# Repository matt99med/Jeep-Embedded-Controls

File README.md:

# Jeep Embedded Controls

A custom embedded security and control system for a 1995 Jeep Wrangler, built as a
personal project to demonstrate full-stack embedded systems development across firmware,
hardware, PCB design, power electronics, and mobile applications.

## Project Overview

This system provides remote control, alarm/immobilization, and real-time GPS tracking
for a 1995 Jeep Wrangler using two custom-designed PCBs, 3D printed enclosures, and a
companion web app. A keyfob and a main controller communicate wirelessly via ESP-NOW,
with 4G LTE cellular for remote GPS tracking accessible from any device.

The system is designed around a **battery-backed, low-power security architecture**: the
controller runs from its own auxiliary battery so it keeps tracking and alarming even if
the vehicle's main battery is disconnected — the exact scenario a theft involves — while
never drawing the vehicle battery down when parked.

## Demo

> Live GPS tracker web app: [Jeep Tracker](https://matt99med.github.io/Jeep-Embedded-Controls/)

## Features

- Remote kill switch (immobilizer) via custom ESP-NOW keyfob
- **Hidden manual bypass switch** — fail-safe so a controller fault never strands the vehicle
- Hood and shock sensor triggered siren with automatic arming
- Remote arm/disarm via keyfob with LED status feedback
- Real-time GPS tracking via 4G LTE cellular (SIM7600G-H)
- Web app for live location tracking via MQTT over HiveMQ Cloud
- **Auxiliary backup battery** — system survives main-battery disconnect
- **Vehicle-sensing charge control** — aux battery charges only while the alternator runs,
  so the vehicle battery is never drained while parked (months of standby)
- **Deep-sleep architecture** — wakes on hood/shock/timer events; tens of µA when parked
- Hardware low-voltage disconnect protecting the aux battery from over-discharge
- LiPo battery powered keyfob with USB-C charging

## Hardware

### Main Controller

- **ESP32-WROOM-32E** module (240MHz dual-core, Wi-Fi, BT)
- **CP2102N** USB-to-UART bridge with auto-reset programming circuit (USB-C)
- **SIM7600G-H** 4G LTE + GPS (Waveshare breakout, socketed)
- **Auxiliary battery system:** 12V sealed AGM battery
- **Vehicle-sensing charge relay:** connects vehicle 12V to aux battery only when the
  alternator is running (firmware-controlled, AO3400A driver, off-board relay)
- **Power rails:**
  - LM5164-Q1 wide-Vin synchronous buck (battery -> 3.3V, ~10uA quiescent)
  - MP2307DN buck (battery -> 3.8V for SIM7600, gated by GPIO for sleep)
  - Hardware UVLO low-voltage disconnect on the 3.3V buck
- Relay/fuse box for kill switch + siren (off-board high current)
- BAT54S input clamps + RC filtering on hood/shock sensor inputs
- SMCJ33A TVS protection on 12V inputs
- 4 firmware-controlled status LEDs (system / cellular / armed / fault)
- Custom 2-layer KiCad PCB, 154.5 x 120 mm
- Custom Fusion 360 enclosure (in progress)

### Keyfob

- **ESP32-C3FH4X** (bare QFN32, 160MHz RISC-V, in-package 4MB flash)
- **Johanson 2450AT18A100E-AEC** chip antenna with L-C-L matching network
- 40MHz crystal (NX3225GD-40M)
- MCP73831 LiPo charger IC
- 3.7V LiPo battery
- USB-C charging + native USB programming (GPIO18/19)
- AP2112K-3.3 LDO
- Tactile buttons: Lock, Unlock + BOOT/RESET
- Status LEDs: charge + connection
- Slide power switch
- Custom 2-layer KiCad PCB, 30 x 50 mm
- Custom Fusion 360 enclosure (in progress)

## Tech Stack

| Category        | Technology                            |
| --------------- | ------------------------------------- |
| Firmware        | ESP-IDF v6.0 (C)                      |
| RTOS            | FreeRTOS                              |
| Wireless        | ESP-NOW (keyfob <-> controller)       |
| Cellular        | SIM7600G-H AT commands over UART2     |
| IoT Protocol    | MQTT over TLS (HiveMQ Cloud)          |
| PCB Design      | KiCad 10.0                            |
| 3D Modeling     | Autodesk Fusion 360                   |
| Web App         | HTML/CSS/JavaScript + Google Maps API |
| Version Control | Git/GitHub                            |
| PCB Fabrication | JLCPCB (assembled)                    |

## System Architecture

```
[Keyfob ESP32-C3] <--ESP-NOW 2.4GHz--> [Main ESP32 Controller]
[Lock/Unlock]                            [Kill Switch / Siren]
                                         [Hood + Shock Sensors]
                                         [Aux Battery + Charge Control]
                                         [Hidden Bypass Switch]
                                                 |
                                         [SIM7600G-H Module]
                                                 |
                                      [Hologram IoT SIM / 4G LTE]
                                                 |
                                        [HiveMQ MQTT Broker]
                                                 |
                                     [Web App / iPhone / Any Device]
```

## Power Architecture

```
[Vehicle 12V] --fused--> [Charge Relay] --(only when alternator running)--> [Aux 12V Battery]
                              ^                                                    |
                       [GPIO sense/control]                                        |
                                                                                   v
                                                          +------------------------+
                                                          |                        |
                                                  [LM5164 Buck]            [MP2307 Buck]
                                                   3.3V (always-on,         3.8V (gated,
                                                   UVLO protected)          SIM7600)
                                                          |                        |
                                                  [ESP32 + logic]          [SIM7600G-H]
```

Key property: when parked, the vehicle battery and the aux battery are physically
disconnected. The controller draws only from the aux battery, so the vehicle always
starts no matter how long it sits.

## Firmware Architecture

The main controller firmware is built around a **tiered low-power state machine** rather
than always-on tasks, to achieve months of parked standby on the auxiliary battery.

### Operating Model

- **Deep sleep** is the default parked state — modem off, CPU halted, only RTC wake
  sources armed. Draw is in the tens of uA.
- **Wake sources:** hood sensor (RTC GPIO), shock sensor (RTC GPIO), or a wake timer for
  scheduled MQTT check-ins. The check-in interval shortens automatically when armed.
- **Active window:** after any activity the controller stays in *light sleep* so the
  radio remains listenable, giving near-instant ESP-NOW lock/unlock response. After an
  idle timeout it drops back to deep sleep.
- On every wake the controller reads vehicle + battery voltage, runs charge control, and
  — if armed and triggered — fires the siren, immobilizes, and pushes an alert + GPS
  burst over cellular.

### Kill Relay Logic (fail-safe)

The kill relay is **energized-to-run**: driving the coil HIGH closes the starter circuit
(vehicle can start); LOW immobilizes. A dead controller, dead battery, or cut wire
therefore fails *immobilized*, and the hidden mechanical bypass switch is the recovery
path. The bypass is intentionally not wired to the PCB.

### Charge Control

Firmware closes the charge relay above 13.2 V on the vehicle-sense line (alternator
running) and opens it below 12.8 V, with hysteresis to avoid chatter. The relay coil is
fed from the vehicle side, so charging is physically impossible when the engine is off
regardless of firmware state.

### Source Layout

```
main_controller/main/
├── main.c            # wake-reason dispatch, tiered sleep state machine
├── config.h          # pin map, thresholds, ESP-NOW protocol
├── system_state.h    # shared state + arm/alarm/charge API
├── gpio_handler.c    # ADC sensing, relay control, arm/alarm, charge logic
├── espnow_handler.c  # keyfob command receiver
└── sim7600.c         # modem power sequencing, GPS, MQTT

keyfob/main/
├── main.c            # deep-sleep wake-on-button, send, LED ack, sleep
├── config.h          # pin map + ESP-NOW protocol
├── espnow_keyfob.c   # one-shot ESP-NOW transmit
└── espnow_keyfob.h
```

### ESP-NOW Message Protocol

| Command     | Value | Action                             |
| ----------- | ----- | ---------------------------------- |
| CMD_LOCK    | 0x01  | Arm siren + immobilize (kill LOW)  |
| CMD_UNLOCK  | 0x02  | Disarm + allow run (kill HIGH)     |

### MQTT Topics

| Topic            | Direction   | Payload                     |
| ---------------- | ----------- | --------------------------- |
| jeep/gps/request | App -> ESP32 | "request"                  |
| jeep/gps/data    | ESP32 -> App | {"lat":xx.xxx,"lon":xx.xxx} |
| jeep/status      | ESP32 -> App | "armed" or "disarmed"       |
| jeep/alert       | ESP32 -> App | power-cut / tamper event    |

> Broker credentials and APN are provided via NVS / `idf.py menuconfig`, not committed to
> source.

## PCB Design

### Keyfob PCB

- 2-layer board, 30 x 50 mm
- All 0402 passives, JLCPCB assembled
- Bare ESP32-C3FH4X with Johanson chip antenna + matching network
- GND copper pour on B.Cu with via stitching
- M2 mounting holes
- USB-C edge connector for charging + programming
- **Status: ordered from JLCPCB (assembled) — awaiting delivery**

### Main Controller PCB

- 2-layer board, 154.5 x 120 mm
- Automotive environment rated design
- Bare ESP32-WROOM-32E + CP2102N programming
- Dual switching power supplies (LM5164 + MP2307)
- Aux battery charge management + UVLO
- Screw-terminal field wiring, socketed SIM7600 carrier
- GND copper pour on B.Cu with via stitching
- M3 mounting holes in all 4 corners
- **Status: ordered from JLCPCB (assembled) — awaiting delivery**

## Status

- [x] Hardware redesign complete (KiCad schematics — both boards, bare-chip)
- [x] Battery-backed power architecture with vehicle-sensing charge control
- [x] Firmware rework for deep-sleep / charge-control architecture
- [x] Keyfob PCB ordered (JLCPCB assembled)
- [x] Main controller PCB ordered (JLCPCB assembled)
- [ ] PCB bring-up and board-level testing
- [ ] SIM7600 MQTT/cellular integration (broker connect + report cycle)
- [ ] 3D printed enclosures (Fusion 360 — in progress)
- [ ] Hidden bypass switch installation
- [ ] System integration and testing
- [ ] Final installation in 1995 Jeep Wrangler

## Author

**Matthew Medina**

California State University Fullerton — BS/MS Computer Engineering

GitHub: [matt99med](https://github.com/matt99med)

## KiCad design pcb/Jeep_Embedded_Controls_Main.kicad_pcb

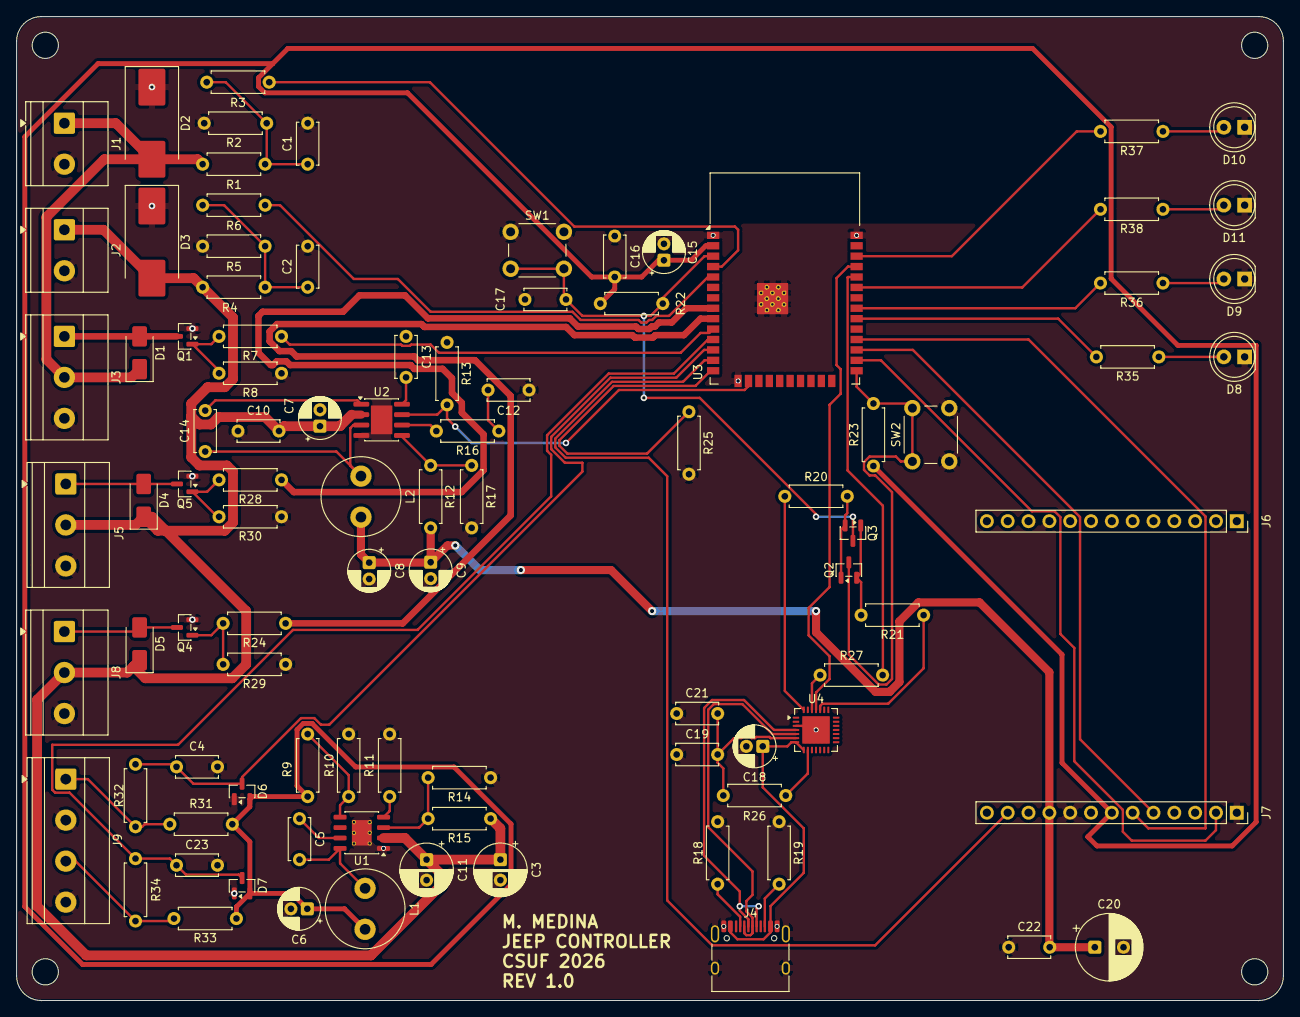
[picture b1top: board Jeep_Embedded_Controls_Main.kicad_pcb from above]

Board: 2 copper layers, 154.5 x 120.0 mm, 94 parts (0 on the bottom side), 63 nets.

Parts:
C1, C2, C4, C10, C13, C16, C19, C22, C23: 100nF; C_Disc_D5.0mm_W2.5mm_P5.00mm
C3: 2.2uF 100V; CP_Radial_D6.3mm_P2.50mm
C5: 100nF 16V; C_Disc_D5.0mm_W2.5mm_P5.00mm
C6: 47uF 10V; CP_Radial_D5.0mm_P2.00mm
C7: 10uF 25V; CP_Radial_D5.0mm_P2.00mm
C8, C9: 22uF 10V; CP_Radial_D5.0mm_P2.00mm
C11: 100uF; CP_Radial_D6.3mm_P2.50mm
C12: 3.9nF; C_Disc_D5.0mm_W2.5mm_P5.00mm
C14: 10nF; C_Disc_D5.0mm_W2.5mm_P5.00mm
C15, C18: 10uF; CP_Radial_D5.0mm_P2.00mm
C17, C21: 1uF; C_Disc_D5.0mm_W2.5mm_P5.00mm
C20: 220uF; CP_Radial_D8.0mm_P3.50mm
D1, D4, D5: SS14; D_SMA
D2, D3: SMCJ33A; D_SMC_Handsoldering
D6, D7: BAT54S; SOT-23
D8: D_SYS; LED_D5.0mm
D9: D_CELL; LED_D5.0mm
D10: D_ARM; LED_D5.0mm
D11: D_FAULT; LED_D5.0mm
J1: VBAT; TerminalBlock_Phoenix_MKDS-1,5-2_1x02_P5.00mm_Horizontal
J2: VAUX; TerminalBlock_Phoenix_MKDS-1,5-2_1x02_P5.00mm_Horizontal
J3: VCHARGE; TerminalBlock_Phoenix_MKDS-1,5-3_1x03_P5.00mm_Horizontal
J4: USB_C_Receptacle_USB2.0_16P; USB_C_Receptacle_HRO_TYPE-C-31-M-12
J5: KILL_SWITCH; TerminalBlock_Phoenix_MKDS-1,5-3_1x03_P5.00mm_Horizontal
J6: SIM7600X_LEFT; PinSocket_1x13_P2.54mm_Vertical
J7: SIM7600X_RIGHT; PinSocket_1x13_P2.54mm_Vertical
J8: SIREN; TerminalBlock_Phoenix_MKDS-1,5-3_1x03_P5.00mm_Horizontal
J9: SW_HOOD; TerminalBlock_Phoenix_MKDS-1,5-4_1x04_P5.00mm_Horizontal
L1: 100uH; L_Radial_D9.5mm_P5.00mm_Fastron_07HVP
L2: 10uH; L_Radial_D9.5mm_P5.00mm_Fastron_07HVP
Q1, Q4, Q5: AO3400A; SOT-23
Q2, Q3: MMBT3904; SOT-23
R1, R4, R15: 1M; R_Axial_DIN0207_L6.3mm_D2.5mm_P7.62mm_Horizontal
R2, R5: 220k; R_Axial_DIN0207_L6.3mm_D2.5mm_P7.62mm_Horizontal
R3, R6, R17, R20, R21, R22, R23, R26, R31, R33: 10k; R_Axial_DIN0207_L6.3mm_D2.5mm_P7.62mm_Horizontal
R7, R24, R28: 100; R_Axial_DIN0207_L6.3mm_D2.5mm_P7.62mm_Horizontal
R8, R11, R13, R25, R29, R30: 100k; R_Axial_DIN0207_L6.3mm_D2.5mm_P7.62mm_Horizontal
R9: 432k; R_Axial_DIN0207_L6.3mm_D2.5mm_P7.62mm_Horizontal
R10: 249k; R_Axial_DIN0207_L6.3mm_D2.5mm_P7.62mm_Horizontal
R12: 30.9k; R_Axial_DIN0207_L6.3mm_D2.5mm_P7.62mm_Horizontal
R14: 150k; R_Axial_DIN0207_L6.3mm_D2.5mm_P7.62mm_Horizontal
R16: 6.8k; R_Axial_DIN0207_L6.3mm_D2.5mm_P7.62mm_Horizontal
R18, R19: 5.1k; R_Axial_DIN0207_L6.3mm_D2.5mm_P7.62mm_Horizontal
R27: 470; R_Axial_DIN0207_L6.3mm_D2.5mm_P7.62mm_Horizontal
R32, R34, R35, R36, R37, R38: 1k; R_Axial_DIN0207_L6.3mm_D2.5mm_P7.62mm_Horizontal
SW1: EN/Reset; SW_PUSH_6mm
SW2: GPIO0/Boot; SW_PUSH_6mm
U1: LM5164DDA; HSOP-8-1EP_3.9x4.9mm_P1.27mm_EP2.41x3.1mm_ThermalVias
U2: MP2307DN-LF-Z; SOIC-8-1EP_3.9x4.9mm_P1.27mm_EP2.62x3.51mm
U3: ESP32-WROOM-32E; ESP32-WROOM-32D
U4: CP2102N-Axx-xQFN28; QFN-28-1EP_5x5mm_P0.5mm_EP3.35x3.35mm

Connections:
3V8_SIM: C8.1, C9.1, C20.1, C22.2, J7.10, L2.2, R12.2
+3.3V: C6.1, C15.1, C16.2, D6.2 (K), D7.2 (K), J7.7, L1.2, R9.2, R22.1, R23.1, R31.1, R33.1, U3.2 (VDD)
/Vehicle Interface and Charging/CHG_COIL: D1.2 (A), J3.1, Q1.3 (D)
/Vehicle Interface and Charging/VEH_12V: D1.1 (K), D2.2 (C), J1.1, J3.2, R1.1
AUX_12V: C3.1, C7.1, C10.2, C11.1, D3.2 (C), D4.1 (K), D5.1 (K), J2.1, J5.2, J8.2, R4.1, R15.1, U1.2 (VIN), U2.2 (IN)
BATT_SENSE: R6.2, U3.5 (SENSOR_VN)
CHG_EN: R7.1, U3.10 (IO25)
GND: C1.2, C2.2, C3.2, C4.1, C6.2, C7.2, C8.2, C9.2, C10.1, C11.2, C12.1, C13.1, C15.2, C16.1, C17.1, C18.2, C19.1, C20.2, C21.1, C22.1, C23.2, D2.1 (A), D3.1 (A), D6.1 (A), D7.1 (A), D8.1 (K), D9.1 (K), D10.1 (K), D11.1 (K), J1.2, J2.2, J3.3, J4.A1 (GND), J4.A12 (GND), J4.B1 (GND), J4.B12 (GND), J4.SH (SHIELD), J5.3, J6.10 (Pin_10_10), J7.1, J7.9, J8.3, J9.2, J9.4, Q1.2 (S), Q4.2 (S), Q5.2 (S), R2.2, R5.2, R8.1, R10.2, R11.1, R13.1, R14.1, R17.2, R18.2, R19.1, R25.2, R29.1, R30.1, SW1.1, SW2.2, U1.1 (GND), U1.9 (EP), U2.4 (GND), U2.9 (EP), U3.1 (GND), U3.15 (GND), U3.38 (GND), U3.39 (GND), U4.3 (GND), U4.29 (GND)
HOOD_SW: C4.2, D6.3 (COM), R32.1, U3.12 (IO27)
KILL_COIL: R28.1, U3.8 (IO32)
unnamed: C1.1, R1.2, R2.1, R3.1
unnamed: C2.1, R4.2, R5.1, R6.1
unnamed: C12.2, R16.1
unnamed: D4.2 (A), J5.1, Q5.3 (D)
unnamed: D5.2 (A), J8.1, Q4.3 (D)
unnamed: D8.2 (A), R35.1
unnamed: D9.2 (A), R36.1
unnamed: D10.2 (A), R37.1
unnamed: D11.2 (A), R38.1
unnamed: J4.A5 (CC1), R18.1
unnamed: J4.B5 (CC2), R19.2
unnamed: J7.2, U3.26 (IO4)
unnamed: J7.5, U3.27 (IO16)
unnamed: J7.6, U3.28 (IO17)
unnamed: J7.12, U3.13 (IO14)
unnamed: J9.1, R31.2, R32.2
unnamed: J9.3, R33.2, R34.1
unnamed: Q1.1 (G), R7.2, R8.2
unnamed: Q2.1 (B), Q3.2 (E), R20.2
unnamed: Q2.3 (C), R23.2, SW2.1, U3.25 (IO0)
unnamed: Q2.2 (E), Q3.1 (B), R21.2
unnamed: C17.2, Q3.3 (C), R22.2, SW1.2, U3.3 (EN)
unnamed: Q4.1 (G), R24.2, R29.2
unnamed: Q5.1 (G), R28.2, R30.2
unnamed: C5.1, U1.7 (BST)
unnamed: R14.2, R15.2, U1.3 (EN/UVLO)
unnamed: R9.1, R10.1, U1.5 (FB)
unnamed: R11.2, U1.4 (RON)
unnamed: C5.2, L1.1, U1.8 (SW)
unnamed: C14.2, U2.1 (BS)
unnamed: R16.2, U2.6 (COMP)
unnamed: R12.1, R17.1, U2.5 (FB)
unnamed: C13.2, U2.8 (SS)
unnamed: C14.1, L2.1, U2.3 (SW)
unnamed: R25.1, U3.14 (IO12)
unnamed: R35.2, U3.30 (IO18)
unnamed: R36.2, U3.31 (IO19)
unnamed: R38.2, U3.33 (IO21)
unnamed: R37.2, U3.36 (IO22)
unnamed: J4.A6 (D+), J4.B6 (D+), U4.4 (D+)
unnamed: J4.A7 (D-), J4.B7 (D-), U4.5 (D-)
unnamed: R27.1, U4.26 (TXD)
unnamed: C18.1, J4.A4 (VBUS), J4.A9 (VBUS), J4.B4 (VBUS), J4.B9 (VBUS), U4.7 (VREGIN), U4.8 (VBUS)
unnamed: C19.2, C21.2, R26.1, U4.6 (VDD)
unnamed: R20.1, U4.28 (~DTR)
unnamed: R26.2, U4.9 (~RST)
unnamed: R21.1, U4.24 (~RTS)
RXD: U3.35 (TXD0/IO1), U4.25 (RXD)
SHOCK_SW: C23.1, D7.3 (COM), R34.2, U3.11 (IO26)
SIM_PWR_EN: R13.2, U2.7 (EN), U3.16 (IO13)
SIREN_COIL: R24.1, U3.9 (IO33)
TXD: R27.2, U3.34 (RXD0/IO3)
VEH_SENSE: R3.2, U3.4 (SENSOR_VP)

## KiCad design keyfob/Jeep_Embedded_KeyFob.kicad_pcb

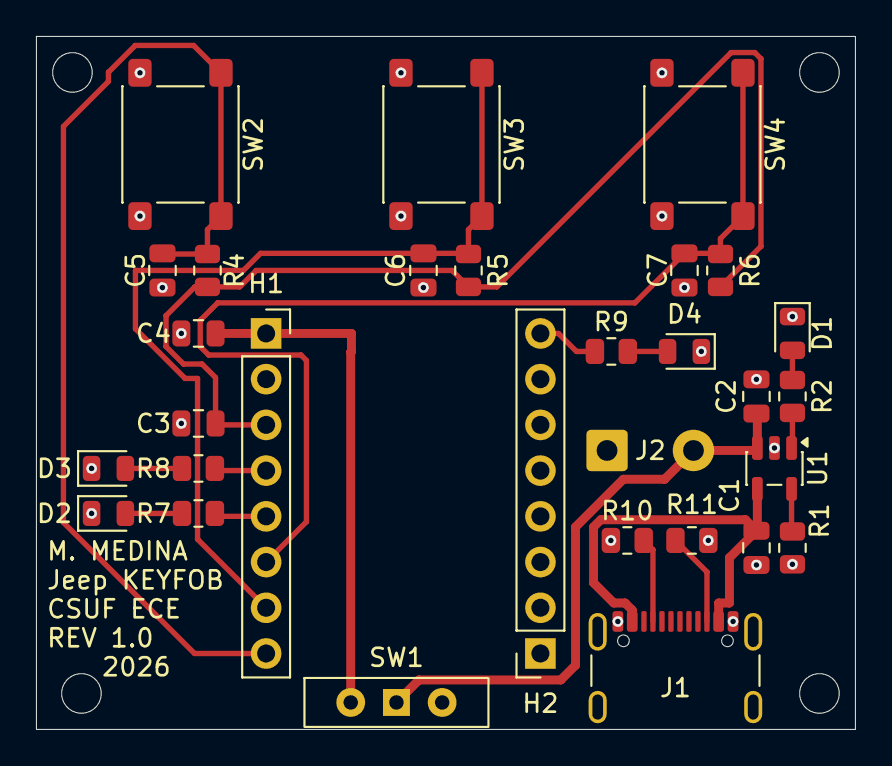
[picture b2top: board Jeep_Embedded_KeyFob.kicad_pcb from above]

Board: 2 copper layers, 45.5 x 38.5 mm, 31 parts (0 on the bottom side), 19 nets.

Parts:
C1: 4.7 uF; C_0805_2012Metric
C2: 1 uF; C_0805_2012Metric
C3, C5, C6, C7: 100 nF; C_0805_2012Metric
C4: 10 uF; C_0805_2012Metric
D1: Yellow/Green; LED_0805_2012Metric
D2: Red; LED_0805_2012Metric
D3: Green; LED_0805_2012Metric
D4: Blue; LED_0805_2012Metric
H1, H2: Conn_01x08_Socket; PinSocket_1x08_P2.54mm_Vertical
J1: USB_C_Receptacle_PowerOnly_6P; USB_C_Receptacle_GCT_USB4105-xx-A_16P_TopMnt_Horizontal
J2: Conn_01x02_Socket; SolderWire-0.5sqmm_1x02_P4.8mm_D0.9mm_OD2.3mm
R1, R4, R5, R6: 10 k; R_0805_2012Metric
R2: 1 k; R_0805_2012Metric
R7, R8: 330; R_0805_2012Metric
R9: 100; R_0805_2012Metric
R10, R11: 5.1 k; R_0805_2012Metric
SW1: SW_Wuerth_450301014042; SW_Slide-03_Wuerth-WS-SLTV_10x2.5x6.4_P2.54mm
SW2, SW3, SW4: SW_SPST; SW_SPST_PTS645Sx43SMTR92
U1: MCP73831-2-OT; SOT-23-5
t: MountingHole_2.2mm_M2

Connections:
3.3V: C3.1, H1.3, R4.1, R5.2, R6.2
BTN_LOCK: C5.1, H1.8, R4.2, SW2.1 (A)
BTN_PANIC: C7.1, H1.6, R6.1, SW4.1 (A)
BTN_UNLOCK: C6.1, H1.7, R5.1, SW3.1 (A)
GND: C1.2, C2.2, C3.2, C4.2, C5.2, C6.2, C7.2, D1.1 (K), D2.1 (K), D3.1 (K), D4.1 (K), H1.2, J1.A1, J1.A12 (GND), J1.B1, J1.B12 (GND), J2.1, R1.1, R10.1, R11.2, SW2.2 (B), SW3.2 (B), SW4.2 (B), U1.2 (V_{SS})
LED_BLUE: H2.8 (Pin_8_8), R9.1
LED_GREEN: H1.4, R8.1
LED_RED: H1.5, R7.1
unnamed: D1.2 (A), R2.1
unnamed: D2.2 (A), R7.2
unnamed: D3.2 (A), R8.2
unnamed: D4.2 (A), R9.2
unnamed: J1.A5 (CC1), R10.2
unnamed: J1.B5 (CC2), R11.1
unnamed: R1.2, U1.5 (PROG)
unnamed: R2.2, U1.1 (STAT)
VBAT: C2.1, J2.2, SW1.1 (B), U1.3 (V_{BAT})
VBAT_SW: C4.1, H1.1, SW1.2 (C)
VBUS: C1.1, J1.A4, J1.A9 (VBUS), J1.B4, J1.B9 (VBUS), U1.4 (V_{DD})

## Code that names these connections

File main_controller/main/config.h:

/*
 * config.h - Jeep Embedded Controls : Main Controller
 * Central hardware + behavior configuration.
 *
 * Target: ESP32-WROOM-32E  (ESP-IDF v6.x, FreeRTOS)
 *
 * All pin numbers verified against schematic
 * "Jeep_Embedded_Controls_Main" rev "Update".
 *
 * NOTE ON SAFETY-CRITICAL CONSTANTS:
 *   KILL relay is ENERGIZED-TO-RUN. Driving KILL_COIL HIGH energizes the
 *   relay coil and CLOSES the starter circuit (vehicle can start). Driving
 *   it LOW de-energizes -> vehicle immobilized. A dead controller therefore
 *   fails immobilized; the hidden mechanical BYPASS switch is the recovery
 *   path and is intentionally NOT wired to this board.
 */
#pragma once

#include "driver/gpio.h"

/* ------------------------------------------------------------------ */
/* GPIO ASSIGNMENTS  (from schematic)                                  */
/* ------------------------------------------------------------------ */

/* --- Analog sense (ADC1, input-only pins) --- */
#define PIN_VEH_SENSE      GPIO_NUM_36   /* SENSOR_VP - vehicle 12V divider */
#define PIN_BATT_SENSE     GPIO_NUM_39   /* SENSOR_VN - aux battery divider */
#define ADC_CH_VEH         ADC_CHANNEL_0 /* GPIO36 = ADC1_CH0 */
#define ADC_CH_BATT        ADC_CHANNEL_3 /* GPIO39 = ADC1_CH3 */

/* --- Charge control --- */
#define PIN_CHG_EN         GPIO_NUM_25   /* HIGH = close charge relay        */

/* --- SIM7600 (Waveshare carrier) --- */
#define PIN_SIM_PWR_EN     GPIO_NUM_13   /* HIGH = enable MP2307 3.8V rail   */
#define PIN_SIM_PWRKEY     GPIO_NUM_14   /* power-on toggle (see sequence)   */
#define PIN_SIM_DTR        GPIO_NUM_4    /* sleep/wake control (optional)    */
#define PIN_SIM_RX         GPIO_NUM_16   /* ESP RX  <- modem TXD             */
#define PIN_SIM_TX         GPIO_NUM_17   /* ESP TX  -> modem RXD             */
#define SIM_UART_PORT      UART_NUM_2

/* --- Sensor inputs (RTC-capable -> can wake from deep sleep) --- */
#define PIN_HOOD_SW        GPIO_NUM_27   /* idle HIGH, LOW = hood open       */
#define PIN_SHOCK_SW       GPIO_NUM_26   /* idle HIGH, LOW = impact pulse    */

/* --- Relay coil drivers (low-side N-FET; HIGH = energized) --- */
#define PIN_KILL_COIL      GPIO_NUM_32   /* HIGH = RUN-enabled, LOW = killed */
#define PIN_SIREN_COIL     GPIO_NUM_33   /* HIGH = siren on                  */

/* --- Status LEDs (HIGH = on; dark by default to protect sleep budget) --- */
#define PIN_LED_SYS        GPIO_NUM_19
#define PIN_LED_CELL       GPIO_NUM_18
#define PIN_LED_ARM        GPIO_NUM_21
#define PIN_LED_FAULT      GPIO_NUM_22

/* ------------------------------------------------------------------ */
/* LOGIC LEVELS                                                        */
/* ------------------------------------------------------------------ */
#define RELAY_ON           1
#define RELAY_OFF          0
#define KILL_RUN_ENABLED   1   /* energize coil -> car can start         */
#define KILL_IMMOBILIZED   0
#define SENSOR_IDLE        1   /* pulled high                            */
#define SENSOR_TRIGGERED   0   /* switch closed to ground                */
#define LED_ON             1
#define LED_OFF            0

/* ------------------------------------------------------------------ */
/* ADC SCALING  (divider = 220k / (1M + 220k) = 0.1803)                */
/*   Vpin = Vrail * 0.1803 ; Vrail = Vpin / 0.1803                      */
/* ------------------------------------------------------------------ */
#define DIV_RATIO          0.18033f
#define MV_TO_RAIL(mv)     ((float)(mv) / DIV_RATIO / 1000.0f)  /* -> volts */

/* ------------------------------------------------------------------ */
/* CHARGE CONTROL HYSTERESIS  (vehicle-sense, volts)                   */
/* ------------------------------------------------------------------ */
#define CHG_CLOSE_V        13.20f   /* alternator running -> start charge  */
#define CHG_OPEN_V         12.80f   /* engine off -> disconnect            */

/* ------------------------------------------------------------------ */
/* AUX BATTERY THRESHOLDS  (volts)                                     */
/* ------------------------------------------------------------------ */
#define BATT_LOW_V         12.00f   /* stretch reporting interval          */
#define BATT_CRIT_V        11.50f   /* "going dark" alert + deep sleep only*/
/* Hardware UVLO (LM5164 EN divider) cuts the rail ~11.5V regardless.  */

/* ------------------------------------------------------------------ */
/* VEHICLE-POWER-LOSS DETECTION                                        */
/*   Vehicle sense dropping below this while previously present = the  */
/*   main battery was cut. Highest-value theft signal in the system.   */
/* ------------------------------------------------------------------ */
#define VEH_PRESENT_V      6.00f

/* ------------------------------------------------------------------ */
/* SLEEP / TIMING                                                      */
/* ------------------------------------------------------------------ */
#define ACTIVE_WINDOW_MS       (90 * 1000)   /* stay light-sleep listenable */
#define CHECKIN_INTERVAL_S     (3 * 3600)    /* deep-sleep MQTT check-in     */
#define CHECKIN_INTERVAL_ARMED_S (30 * 60)   /* faster when armed            */
#define PWRKEY_HIGH_MS         500
#define PWRKEY_LOW_MS          1100
#define SENSOR_DEBOUNCE_MS     50

/* ------------------------------------------------------------------ */
/* SIM / MQTT                                                          */
/*   Secrets are NOT stored here. Provide them via menuconfig / NVS.   */
/*   Add a secrets.h (gitignored) or use idf.py menuconfig values.     */
/* ------------------------------------------------------------------ */
#define MQTT_TOPIC_GPS_REQ     "jeep/gps/request"
#define MQTT_TOPIC_GPS_DATA    "jeep/gps/data"
#define MQTT_TOPIC_STATUS      "jeep/status"
#define MQTT_TOPIC_ALERT       "jeep/alert"     /* power-cut / tamper        */

/* ------------------------------------------------------------------ */
/* ESP-NOW COMMAND PROTOCOL  (matches keyfob)                          */
/* ------------------------------------------------------------------ */
typedef enum {
    CMD_LOCK   = 0x01,   /* arm siren + immobilize (KILL_COIL LOW)      */
    CMD_UNLOCK = 0x02,   /* disarm + allow run (KILL_COIL HIGH)         */
} jeep_cmd_t;

/* keyfob -> controller payload */
typedef struct __attribute__((packed)) {
    uint8_t cmd;
    uint8_t seq;          /* rolling counter, replay sanity            */
} espnow_msg_t;

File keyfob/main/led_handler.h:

#ifndef LED_HANDLER_H
#define LED_HANDLER_H

#include "driver/gpio.h"
#include <stdbool.h>

// ─── LED GPIO pins ───────────────────────────────────
#define PIN_LED_RED      GPIO_NUM_3
#define PIN_LED_GREEN    GPIO_NUM_4
#define PIN_LED_BLUE     GPIO_NUM_5

// ─── Function prototypes ────────────────────────────
void led_handler_init(void);
void led_set_red(bool state);
void led_set_green(bool state);
void led_set_blue(bool state);
void led_all_off(void);
void led_show_armed(void);
void led_show_disarmed(void);
void led_show_panic(void);
void led_show_sending(void);

#endif // LED_HANDLER_H

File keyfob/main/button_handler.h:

#ifndef BUTTON_HANDLER_H
#define BUTTON_HANDLER_H

#include "driver/gpio.h"
#include <stdbool.h>

// ─── Button GPIO pins ────────────────────────────────
#define PIN_BTN_LOCK     GPIO_NUM_0
#define PIN_BTN_UNLOCK   GPIO_NUM_1
#define PIN_BTN_PANIC    GPIO_NUM_2

// ─── Debounce time ───────────────────────────────────
#define BTN_DEBOUNCE_MS  50

// ─── Button states ───────────────────────────────────
typedef enum {
    BTN_NONE   = 0,
    BTN_LOCK   = 1,
    BTN_UNLOCK = 2,
    BTN_PANIC  = 3,
} button_event_t;

// ─── Function prototypes ────────────────────────────
void button_handler_init(void);
button_event_t button_get_event(void);

#endif // BUTTON_HANDLER_H

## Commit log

2026-05-24 Initial project structure - Jeep embedded controls
2026-05-24 Remove root .vscode from tracking
2026-05-24 Add project README
2026-05-24 Fix README code block formatting
2026-05-24 Add gpio_handler for main controller
2026-05-24 Add gpio_handler - all GPIO pin definitions and control functions
2026-05-24 Add espnow_handler - ESP-NOW communication between main controller and keyfob
2026-05-24 Add sim7600 handler - GPS, cellular, and MQTT over AT commands
2026-05-24 Update gitignore and remove IDE artifacts from tracking
2026-05-24 Add keyfob firmware - buttons, LEDs, and ESP-NOW communication
2026-05-24 Fix gitignore and remove all IDE artifacts
2026-05-24 Restore gitignore and remove .vscode permanently
2026-05-24 Update keyfob MAC address in main controller ESP-NOW config
2026-05-24 Add web app - GPS tracker with MQTT and Google Maps
2026-05-24 Move app to root for GitHub Pages hosting
2026-05-24 Add redirect to app from root URL
2026-05-24 Update README status - firmware and web app complete
2026-05-24 Add keyfob PCB layout and Gerber files
2026-05-24 Update README - full project documentation
2026-05-24 Organize keyfob gerbers into gerbers subfolder
2026-05-24 Organize keyfob pcb files
2026-05-24 create an images folder for the 3d view on Kicad
2026-05-29 Update GPIO pins - BLINK moved to GPIO1, SIREN moved to GPIO3
2026-05-29 Add PCB files, updated schematics, and project images
2026-05-29 Update README - PCBs ordered, full project documentation
2026-05-29 Add PCB 3D render images to README
2026-06-14 Update README for bare-chip battery-backed redesign
    - Main controller: ESP32-DevKit V1 -> bare ESP32-WROOM-32E + CP2102N
    - Keyfob: ESP32-C3 Super Mini -> bare ESP32-C3FH4X + Johanson antenna
    - New battery-backed power architecture (aux AGM + vehicle-sensing charge relay)
    - Added hidden bypass kill switch and deep-sleep parked operation
    - Removed 5x aux light control (run separately)
    - Updated power, firmware, and PCB sections
2026-06-14 Rework firmware for battery-backed redesign
    - Main controller: deep-sleep/light-sleep tiered power model
    - Energized-to-run kill relay, hood + shock sensor monitoring
    - Firmware charge control with hysteresis, battery monitoring
    - SIM7600 power sequencing + GPS/MQTT skeleton (creds via NVS)
    - Keyfob: deep-sleep wake-on-button, ESP-NOW one-shot send
    - Remove old dev-board firmware (button_handler, led_handler, light tasks)
2026-06-14 Add firmware source files and .gitignore
2026-06-14 Update README: real firmware architecture, boards ordered
2026-06-14 Working on updating schematics
